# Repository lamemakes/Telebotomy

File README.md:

# Telebotomy

What do you do when your Smart TV is a little _too_ smart - especially when you aren't using it? 

## Protect Your Privacy

Your Smart TV continues to report your data while it's turned "off". The Telebotomy aims to "lobotomize" your Smart TV while it's off by severing it's network connection. It does so by reading the remote control input and acting as a 2-port ethernet switch to allow/block network connections based on input recieved.

For more thorough data protection while using a Smart TV, it is recommended to utilize a [Pi-hole](https://pi-hole.net). There are still pitfalls with this and trackers that can't be blocked, though.

## Requirements

In order to use Telebotomy, a user needs to:

- Use ethernet as the Smart TV's network connection
- Have a compatible remote
    - Currently only IR remotes are supported, but there are plans to extend this.
- Access to a USB power source

## Installation

The installation of the Telebotomy is as follows:

1. Ensure the Smart TV is powered but turned off.
1. Plug in the ethernet to the Telebotomy's respective ports
    - _TV Out_ should be the connection to the TV
    - _Net In_ should be the connection to the network source
1. Locate the _Remote Input_ connector on the Telebotomy and connect the appropriate sensor
    - _If using IR_ place the sensor so it's close to the TV's reciever.
1. Connect the Telebotomy's Micro-USB port to a USB power source.
1. [Test!](#testing-telebotomy)
1. Profit!

## Testing Telebotomy

1. Ensure the Smart TV is powered but turned off.
1. Power cycle the Telebotomy or press the "Reset" button.
1. Turn on the Smart TV utilizing the remote
1. Confirm internet connectivity:
    - LINK & ACT LEDs on the Telebotomy are active
    - The Smart TV can connect to the internet
    - _If using Pi-Hole_ There is network activity coming from the IP of the TV.
1. Turn off the Smart TV utilizing the remote
1. Confirm there is no internet connectivity:
    - LINK & ACT LEDs on the Telebotomy are inactive
    - Turn the TV on via a physical button and ensure it is not connected to the internet
    - _If using Pi-Hole_ There is no network activity coming from the IP of the TV.

## Diagrams

### Schematic

### PCB Layout

<!--

## Protect Your Privacy

Smart TVs are constantly reporting all sorts of data about their owners. While a Smart TV is "turned on", it is likely creating a profile around the user containing assumptions about things like attention span, content interests, ad engagement, and other categories that would be valuable from an ads/content standpoint. Sometimes this is added to existing profiles of the user as Google/Facebook/Amazon are some of the most prevelant ad services.

**But when the TV is off it stops this reporting, right?**

Wrong. While your Smart TV may look off, it's very chatty on the internet. It will continue to gain whatever information it can on a user, it just won't be able to watch viewing patterns. It still has the capability to:
 - Report local WiFi/Bluetooth devices
 - Process microphone audio
 - Determine routines of the user (ie. what time do the lights go out at night?)
 - Continue to report sensitive information like UIDs or a users location (sometimes unencrypted!)

This can be somewhat stopped using tools like [Pi-hole](https://pi-hole.net) but some requests still fall through the cracks. To ensure all unwanted data reporting is stopped, the only real solution is to manually toggle the WiFi or physically plug/unplug the Ethernet to TV every use. This is the issues Telebotomy is hoping to fix!

## How does it work?

Telebotomy acts as a two port network switch that will either allow or disallow the passage of all network packets bidirectionally between the target device and internet source. The Telebotomy works to read the input from your TVs remote, and toggle the internet based on the intended action.

For more info, check out [Watching You Watch: The Tracking Ecosystem of Over-the-Top
TV Streaming Devices](https://tv-watches-you.princeton.edu/tv-tracking-acm-ccs19.pdf).

-->

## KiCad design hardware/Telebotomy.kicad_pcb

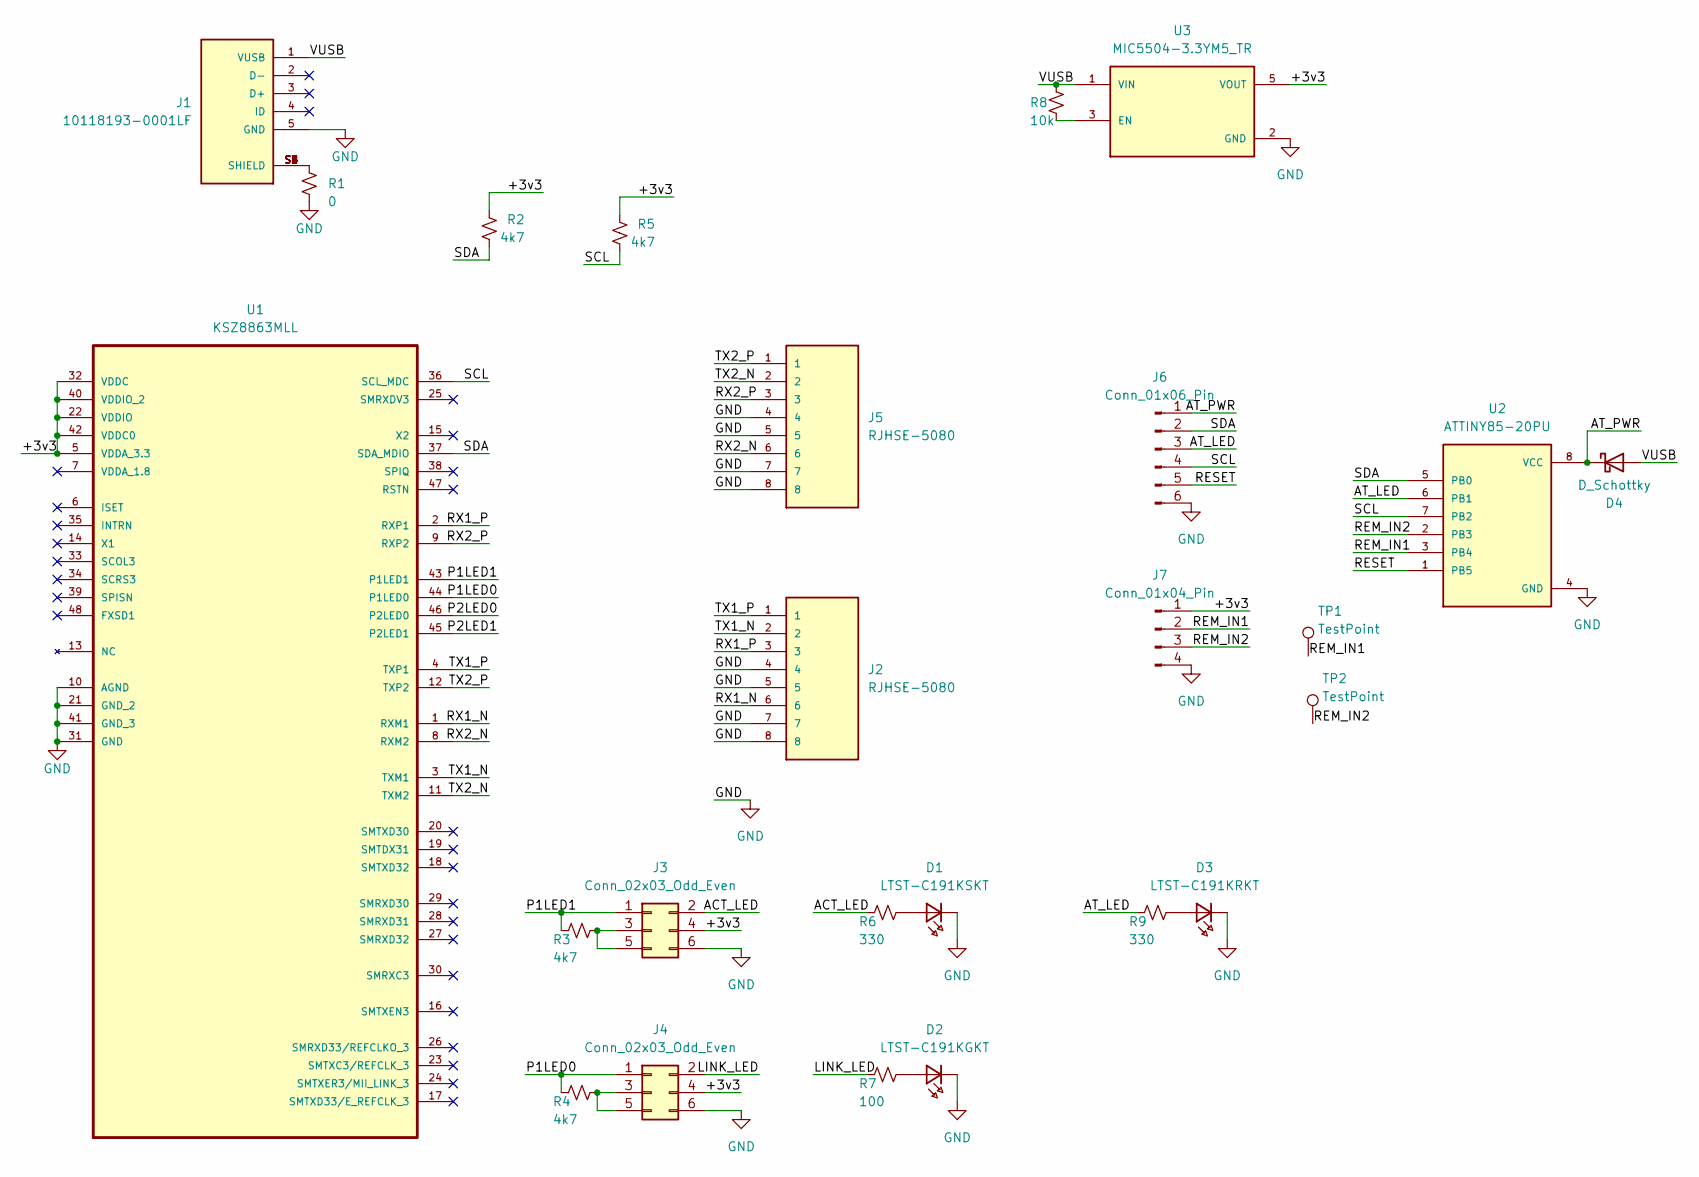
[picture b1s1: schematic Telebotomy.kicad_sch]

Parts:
D1: LTST-C191KSKT; R_0603_1608Metric_Pad0.98x0.95mm_HandSolder; DigiKey_Part_Number 160-1446-2-ND
D2: LTST-C191KGKT; R_0603_1608Metric_Pad0.98x0.95mm_HandSolder; DigiKey_Part_Number 160-1446-2-ND
D3: LTST-C191KRKT; R_0603_1608Metric_Pad0.98x0.95mm_HandSolder; DigiKey_Part_Number 160-1446-2-ND
D4: D_Schottky; 3v3_TVS
J1: 10118193-0001LF; AMPHENOL_10118193-0001LF; PARTREV E; DigiKey_Part_Number 609-4616-2-ND
J2, J5: RJHSE-5080; AMPHENOL_RJHSE-5080; PARTREV G; DigiKey_Part_Number RJHSE-5080-ND
J3, J4: Conn_02x03_Odd_Even; PinHeader_2x03_P2.54mm_Vertical
J6: Conn_01x06_Pin; PinHeader_1x06_P2.54mm_Vertical
J7: Conn_01x04_Pin; PinHeader_1x04_P2.54mm_Vertical
R1: 0; R_0603_1608Metric_Pad0.98x0.95mm_HandSolder
R2, R3, R4, R5: 4k7; R_0603_1608Metric_Pad0.98x0.95mm_HandSolder
R6, R9: 330; R_0603_1608Metric_Pad0.98x0.95mm_HandSolder
R7: 100; R_0603_1608Metric_Pad0.98x0.95mm_HandSolder
R8: 10k; R_0603_1608Metric_Pad0.98x0.95mm_HandSolder
TP1, TP2: TestPoint; TestPoint_Pad_D1.0mm
U1: KSZ8863MLL; QFP50P900X900X160-48N; MPN KSZ8863MLL; DigiKey_Part_Number 576-3577-ND
U2: ATTINY85-20PU; DIP762W46P254L927H533Q8B; DigiKey_Part_Number ATTINY85-20PU-ND
U3: MIC5504-3.3YM5_TR; SOT95P280X145-5N; PARTREV 05/14/19; DigiKey_Part_Number 576-4764-2-ND

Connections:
/+3v3: J3.4, J4.4, J7.1, R2.2, R5.2, U1.5 (VDDA_3.3), U1.22 (VDDIO), U1.32 (VDDC), U1.40 (VDDIO_2), U1.42 (VDDC0), U3.5 (VOUT)
/ACT_LED: J3.2, R6.2
/AT_LED: J6.3, R9.2, U2.6 (PB1)
/AT_PWR: D4.1 (K), J6.1, U2.8 (VCC)
/LINK_LED: J4.2, R7.2
/P1LED0: J4.1, R4.2, U1.44 (P1LED0)
/P1LED1: J3.1, R3.2, U1.43 (P1LED1)
/P2LED0: U1.46 (P2LED0)
/P2LED1: U1.45 (P2LED1)
/REM_IN1: J7.2, TP1.1, U2.3 (PB4)
/REM_IN2: J7.3, TP2.1, U2.2 (PB3)
/RESET: J6.5, U2.1 (PB5)
/RX1_N: J2.6, U1.1 (RXM1)
/RX1_P: J2.3, U1.2 (RXP1)
/RX2_N: J5.6, U1.8 (RXM2)
/RX2_P: J5.3, U1.9 (RXP2)
/SCL: J6.4, R5.1, U1.36 (SCL_MDC), U2.7 (PB2)
/SDA: J6.2, R2.1, U1.37 (SDA_MDIO), U2.5 (PB0)
/TX1_N: J2.2, U1.3 (TXM1)
/TX1_P: J2.1, U1.4 (TXP1)
/TX2_N: J5.2, U1.11 (TXM2)
/TX2_P: J5.1, U1.12 (TXP2)
/VUSB: D4.2 (A), J1.1 (VUSB), R8.1, U3.1 (VIN)
GND: D1.1, D2.1, D3.1, J1.5 (GND), J2.4, J2.5, J2.7, J2.8, J3.6, J4.6, J5.4, J5.5, J5.7, J5.8, J6.6, J7.4, R1.2, U1.10 (AGND), U1.21 (GND_2), U1.31 (GND), U1.41 (GND_3), U2.4 (GND), U3.2 (GND)
unnamed: D1.2, R6.1
unnamed: D2.2, R7.1
unnamed: D3.2, R9.1
unnamed: J1.S1 (SHIELD), J1.S2 (SHIELD), J1.S3 (SHIELD), J1.S4 (SHIELD), J1.S5 (SHIELD), J1.S6 (SHIELD), R1.1
unnamed: J3.3, J3.5, R3.1
unnamed: J4.3, J4.5, R4.1
unnamed: R8.2, U3.3 (EN)

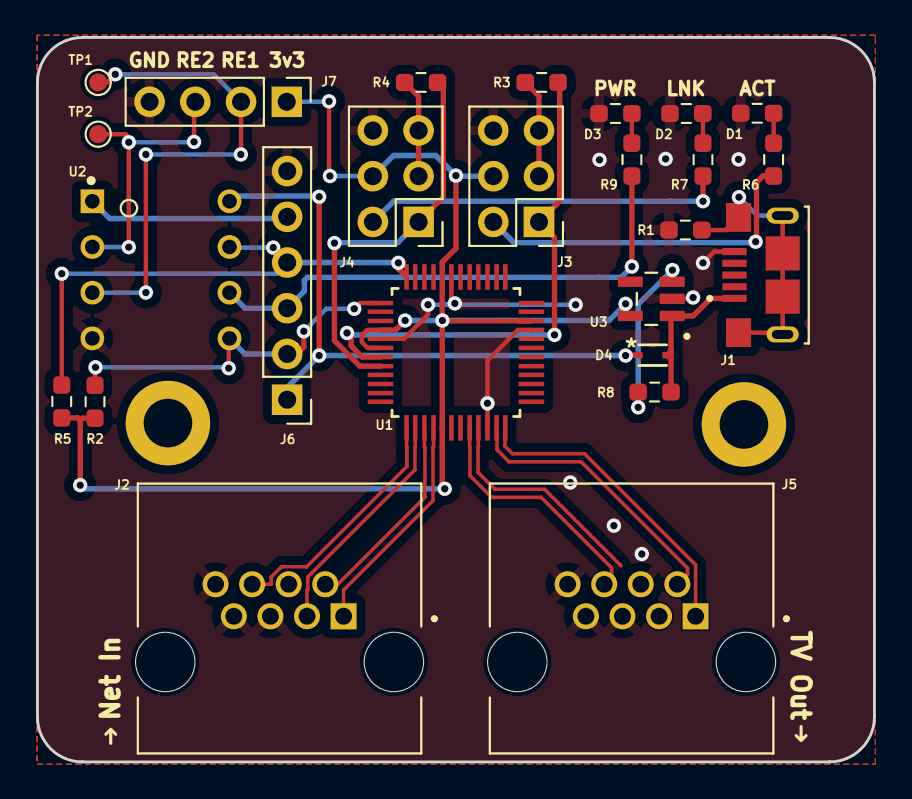
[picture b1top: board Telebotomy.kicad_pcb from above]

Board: 2 copper layers, 46.5 x 40.2 mm, 25 parts (0 on the bottom side), 29 nets.

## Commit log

2023-09-20 Refined schematic and began PCB organization
2023-09-21 Added github workflow to update pic
2023-09-21 Updates Schematic Image
2023-09-21 More fixes to the CI
2023-09-21 Update Schematic Image
2023-09-26 PCB Updates
2023-10-10 Closer to final PCB, updated CI to include snip of PCB
2023-10-10 Merged and removed existing svg
2023-10-10 Workflow fixes
